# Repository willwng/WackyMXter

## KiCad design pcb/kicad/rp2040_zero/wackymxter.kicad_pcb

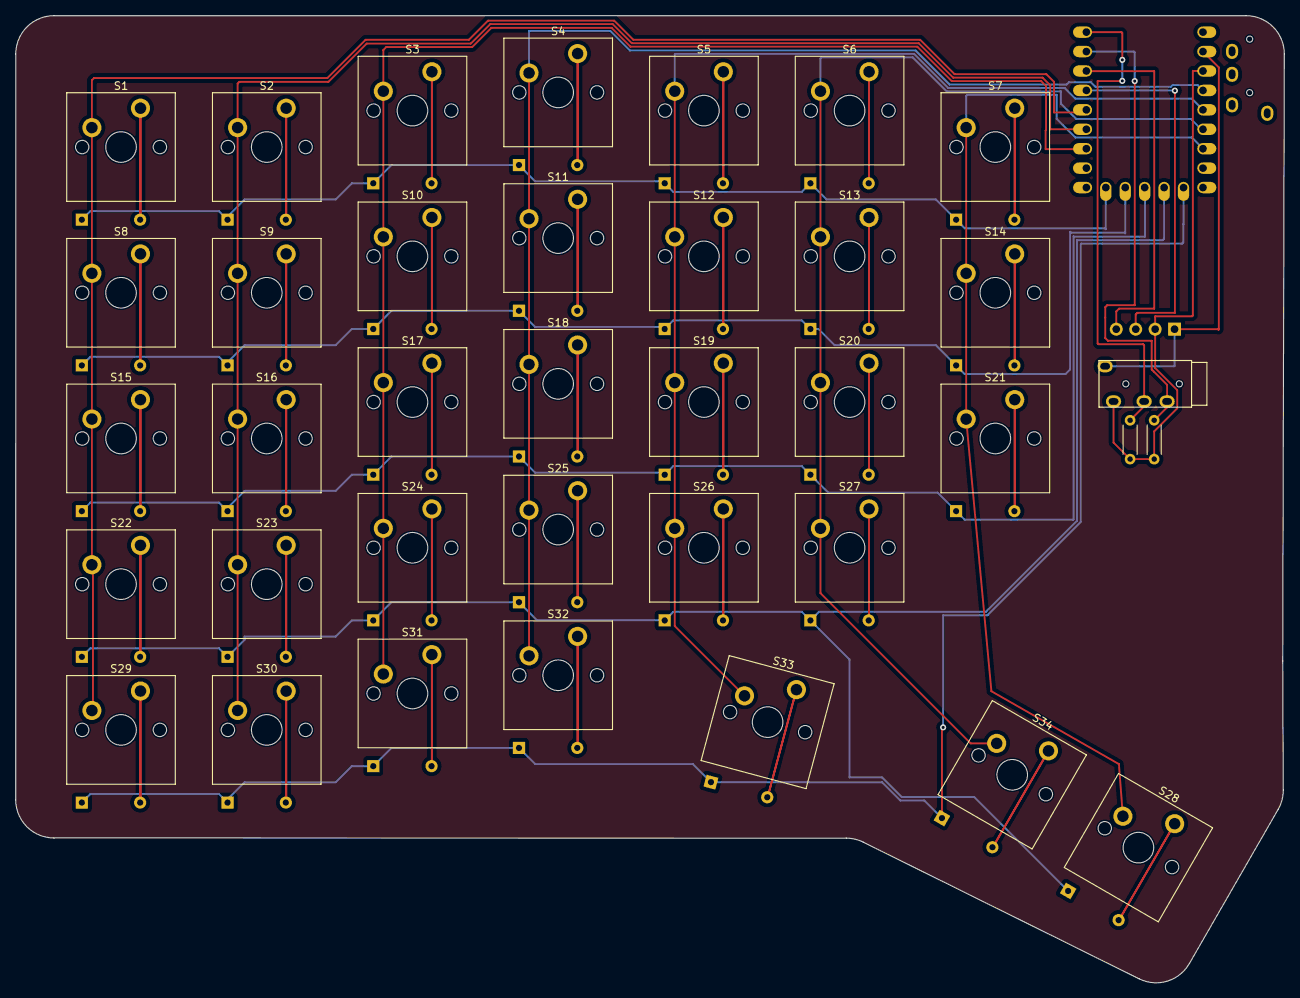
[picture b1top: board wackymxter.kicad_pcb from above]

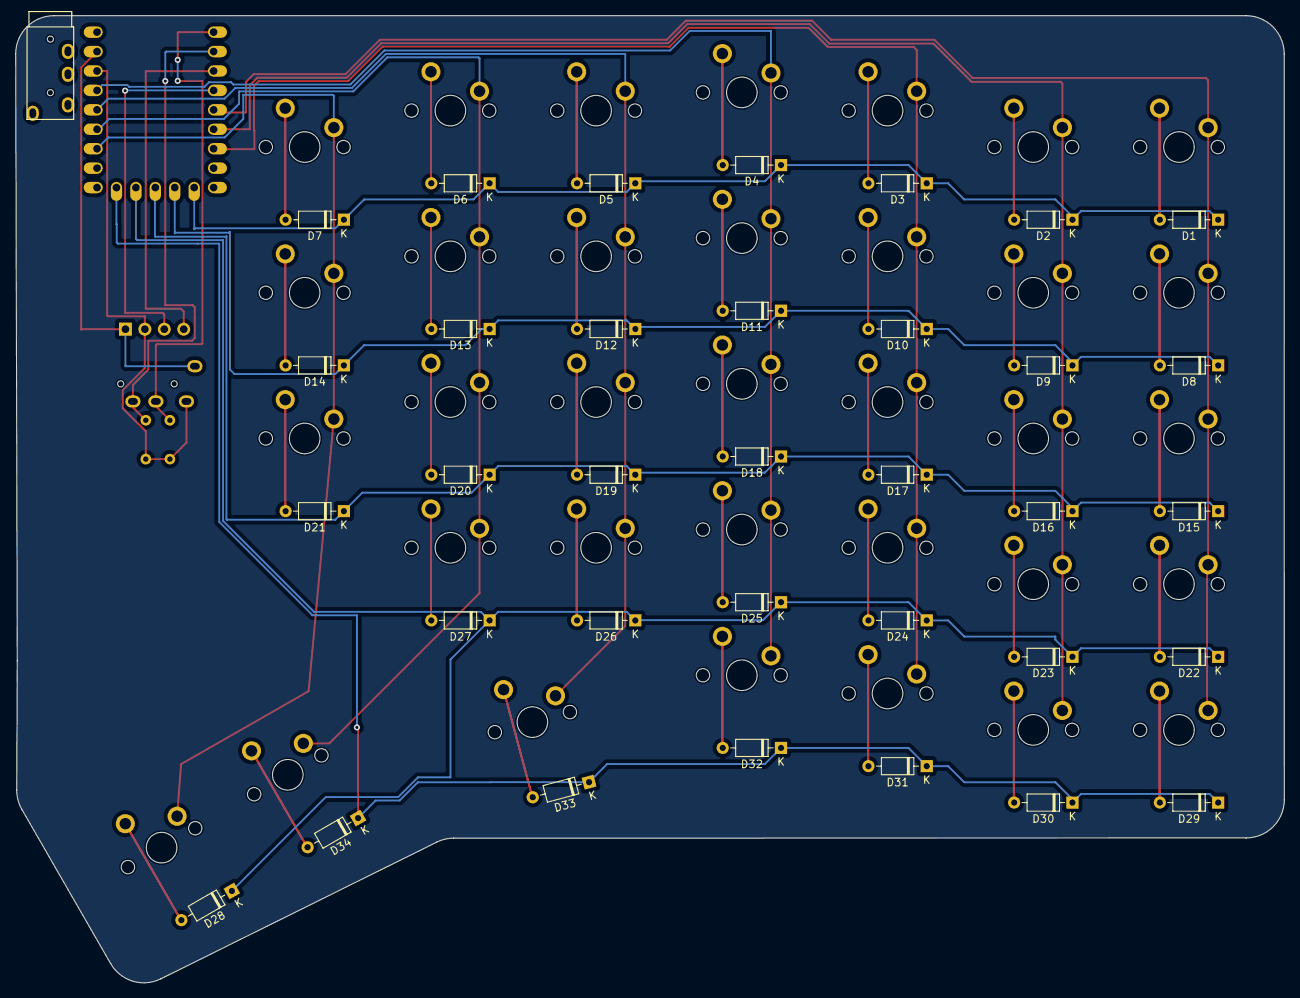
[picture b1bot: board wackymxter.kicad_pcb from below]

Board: 2 copper layers, 165.9 x 126.4 mm, 74 parts (36 on the bottom side), 52 nets.

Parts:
D1, D2, D3, D4, D5, D6, D7, D8, D9, D10, D11, D12, D13, D14, D15, D16, D17, D18, D19, D20, D21, D22, D23, D24, D25, D26, D27, D28, D29, D30, D31, D32, D33, D34: Diode; Diode_DO-35
J1: OLED_128x32
R1, R2: Resistor; R_Axial_DIN0204_L3.6mm_D1.6mm_P5.08mm_Horizontal
S1, S2, S3, S4, S5, S6, S7, S8, S9, S10, S11, S12, S13, S14, S15, S16, S17, S18, S19, S20, S21, S22, S23, S24, S25, S26, S27, S28, S29, S30, S31, S32, S33, S34: Keyswitch; MX_PCB_1.00u
U1: RP2040_Zero
U3, U3#2: TRRS; TRRS_PJ-320A

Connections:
GND: J1.1 (GND), U1.22 (GND), U3.1 (SLEEVE)
unnamed: D1.2 (A), S1.2
unnamed: D2.2 (A), S2.2
unnamed: D3.2 (A), S3.2
unnamed: D4.2 (A), S4.2
unnamed: D5.2 (A), S5.2
unnamed: D6.2 (A), S6.2
unnamed: D7.2 (A), S7.2
unnamed: D8.2 (A), S8.2
unnamed: D9.2 (A), S9.2
unnamed: D10.2 (A), S10.2
unnamed: D11.2 (A), S11.2
unnamed: D12.2 (A), S12.2
unnamed: D13.2 (A), S13.2
unnamed: D14.2 (A), S14.2
unnamed: D15.2 (A), S15.2
unnamed: D16.2 (A), S16.2
unnamed: D17.2 (A), S17.2
unnamed: D18.2 (A), S18.2
unnamed: D19.2 (A), S19.2
unnamed: D20.2 (A), S20.2
unnamed: D21.2 (A), S21.2
unnamed: D22.2 (A), S22.2
unnamed: D23.2 (A), S23.2
unnamed: D24.2 (A), S24.2
unnamed: D25.2 (A), S25.2
unnamed: D26.2 (A), S26.2
unnamed: D27.2 (A), S27.2
unnamed: D28.2 (A), S28.2
unnamed: D29.2 (A), S29.2
unnamed: D30.2 (A), S30.2
unnamed: D31.2 (A), S31.2
unnamed: D32.2 (A), S32.2
unnamed: D33.2 (A), S33.2
unnamed: D34.2 (A), S34.2
RX0: R2.2, U1.2 (1), U3.4 (RING2)
SCL: J1.3 (SCL), U1.4 (3)
SDA: J1.4 (SDA), U1.3 (2)
TX0: R1.2, U1.1 (0), U3.3 (RING1)
VCC: J1.2 (VCC), R1.1, R2.1, U1.21 (3V3), U3.2 (TIP)
col0: S1.1, S8.1, S15.1, S22.1, S29.1, U1.5 (4)
col1: S2.1, S9.1, S16.1, S23.1, S30.1, U1.6 (5)
col2: S3.1, S10.1, S17.1, S24.1, S31.1, U1.7 (6)
col3: S4.1, S11.1, S18.1, S25.1, S32.1, U1.20 (29)
col4: S5.1, S12.1, S19.1, S26.1, S33.1, U1.19 (28)
col5: S6.1, S13.1, S20.1, S27.1, S34.1, U1.18 (27)
col6: S7.1, S14.1, S21.1, S28.1, U1.17 (26)
row0: D1.1 (K), D2.1 (K), D3.1 (K), D4.1 (K), D5.1 (K), D6.1 (K), D7.1 (K), U1.10 (9)
row1: D8.1 (K), D9.1 (K), D10.1 (K), D11.1 (K), D12.1 (K), D13.1 (K), D14.1 (K), U1.11 (10)
row2: D15.1 (K), D16.1 (K), D17.1 (K), D18.1 (K), D19.1 (K), D20.1 (K), D21.1 (K), U1.12 (11)
row3: D22.1 (K), D23.1 (K), D24.1 (K), D25.1 (K), D26.1 (K), D27.1 (K), D28.1 (K), U1.13 (12)
row4: D29.1 (K), D30.1 (K), D31.1 (K), D32.1 (K), D33.1 (K), D34.1 (K), U1.14 (13)
